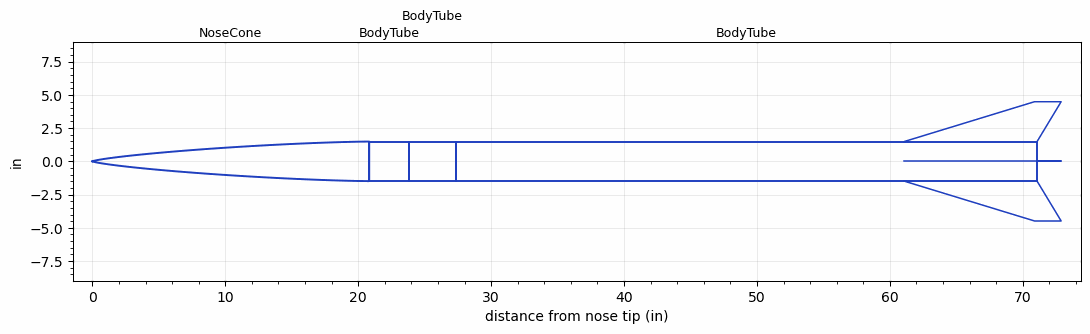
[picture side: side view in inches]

<RASAeroDocument>
 <FileVersion>2</FileVersion>
 <RocketDesign>
  <NoseCone>
   <Length>20.825</Length>
   <Diameter>2.975</Diameter>
   <Shape>Von Karman Ogive</Shape>
   <BluntRadius>0.025</BluntRadius>
   <Location>0</Location>
  </NoseCone>
  <BodyTube>
   <Length>3</Length>
   <Diameter>2.975</Diameter>
   <Location>20.825</Location>
  </BodyTube>
  <BodyTube>
   <Length>3.5</Length>
   <Diameter>2.975</Diameter>
   <Location>23.825</Location>
  </BodyTube>
  <BodyTube>
   <Length>43.748</Length>
   <Diameter>2.975</Diameter>
   <Location>27.325</Location>
   <Fin>
    <Count>4</Count>
    <Chord>10</Chord>
    <Span>3</Span>
    <SweepDistance>9.8125</SweepDistance>
    <TipChord>2</TipChord>
    <Thickness>0.24</Thickness>
    <LERadius>0.03</LERadius>
    <Location>10</Location>
    <AirfoilSection>Hexagonal</AirfoilSection>
    <FX1>0.9212</FX1>
    <FX3>0.9212</FX3>
   </Fin>
  </BodyTube>
  <Surface>Rough Camouflage Paint</Surface>
  <ModifiedBarrowman>True</ModifiedBarrowman>
  <Turbulence>True</Turbulence>
  <UseBooster1>False</UseBooster1>
  <UseBooster2>False</UseBooster2>
 </RocketDesign>
 <LaunchSite>
  <Altitude>3900</Altitude>
  <Pressure>0</Pressure>
  <RodAngle>0</RodAngle>
  <RodLength>10</RodLength>
  <Temperature>70</Temperature>
  <WindSpeed>5</WindSpeed>
 </LaunchSite>
 <Recovery>
  <Altitude1>3000</Altitude1>
  <Altitude2>2000</Altitude2>
  <DeviceType1>Parachute</DeviceType1>
  <DeviceType2>Parachute</DeviceType2>
  <Event1>False</Event1>
  <Event2>False</Event2>
  <Size1>24</Size1>
  <Size2>9</Size2>
  <EventType1>Altitude</EventType1>
  <EventType2>Apogee</EventType2>
  <CD1>2.1</CD1>
  <CD2>0.8</CD2>
 </Recovery>
 <MachAlt>
  <Item>0, 5000</Item>
  <Item>4.5, 60000</Item>
 </MachAlt>
 <SimulationList>
  <Simulation>
   <SustainerEngine>N3570CE  (Chase)</SustainerEngine>
   <SustainerLaunchWt>24.5</SustainerLaunchWt>
   <SustainerNozzleDiameter>2.5</SustainerNozzleDiameter>
   <SustainerCG>43</SustainerCG>
   <SustainerIgnitionDelay>0</SustainerIgnitionDelay>
   <Booster1SeparationDelay>0</Booster1SeparationDelay>
   <Booster1IgnitionDelay>0</Booster1IgnitionDelay>
   <IncludeBooster1>False</IncludeBooster1>
   <Booster2Delay>0</Booster2Delay>
   <IncludeBooster2>False</IncludeBooster2>
   <TimetoApogee>54.63684</TimetoApogee>
   <MaxAltitude>63061.08</MaxAltitude>
   <MaxVelocity>3898.808</MaxVelocity>
   <OptimumWt>20.825</OptimumWt>
   <OptimumMaxAlt>20.825</OptimumMaxAlt>
  </Simulation>
  <Simulation>
   <SustainerEngine>N2500CP  (Chase)</SustainerEngine>
   <SustainerLaunchWt>22</SustainerLaunchWt>
   <SustainerNozzleDiameter>2.5</SustainerNozzleDiameter>
   <SustainerCG>42.6</SustainerCG>
   <SustainerIgnitionDelay>0</SustainerIgnitionDelay>
   <Booster1SeparationDelay>0</Booster1SeparationDelay>
   <Booster1IgnitionDelay>0</Booster1IgnitionDelay>
   <IncludeBooster1>False</IncludeBooster1>
   <Booster2Delay>0</Booster2Delay>
   <IncludeBooster2>False</IncludeBooster2>
   <TimetoApogee>66.01569</TimetoApogee>
   <MaxAltitude>84387.34</MaxAltitude>
   <MaxVelocity>4372.384</MaxVelocity>
  </Simulation>
  <Simulation>
   <SustainerEngine>N2900CB  (Chase)</SustainerEngine>
   <SustainerLaunchWt>24.2</SustainerLaunchWt>
   <SustainerNozzleDiameter>2.5</SustainerNozzleDiameter>
   <SustainerCG>43.1</SustainerCG>
   <SustainerIgnitionDelay>0</SustainerIgnitionDelay>
   <Booster1SeparationDelay>0</Booster1SeparationDelay>
   <Booster1IgnitionDelay>0</Booster1IgnitionDelay>
   <IncludeBooster1>False</IncludeBooster1>
   <Booster2Delay>0</Booster2Delay>
   <IncludeBooster2>False</IncludeBooster2>
   <TimetoApogee>59.35604</TimetoApogee>
   <MaxAltitude>71313.13</MaxAltitude>
   <MaxVelocity>4221.602</MaxVelocity>
   <OptimumWt>20.99331</OptimumWt>
   <OptimumMaxAlt>20.99331</OptimumMaxAlt>
  </Simulation>
  <Simulation>
   <SustainerEngine>N2600CE  (Chase)</SustainerEngine>
   <SustainerLaunchWt>22</SustainerLaunchWt>
   <SustainerNozzleDiameter>2.5</SustainerNozzleDiameter>
   <SustainerCG>43.23</SustainerCG>
   <SustainerIgnitionDelay>0</SustainerIgnitionDelay>
   <Booster1SeparationDelay>0</Booster1SeparationDelay>
   <Booster1IgnitionDelay>0</Booster1IgnitionDelay>
   <IncludeBooster1>False</IncludeBooster1>
   <Booster2Delay>0</Booster2Delay>
   <IncludeBooster2>False</IncludeBooster2>
   <TimetoApogee>56.73648</TimetoApogee>
   <MaxAltitude>70116.66</MaxAltitude>
   <MaxVelocity>4839.931</MaxVelocity>
   <OptimumWt>18.615</OptimumWt>
   <OptimumMaxAlt>18.615</OptimumMaxAlt>
  </Simulation>
  <Simulation>
   <SustainerEngine>N3570CE  (Chase)</SustainerEngine>
   <SustainerLaunchWt>20.4</SustainerLaunchWt>
   <SustainerNozzleDiameter>2.5</SustainerNozzleDiameter>
   <SustainerCG>43.48</SustainerCG>
   <SustainerIgnitionDelay>0</SustainerIgnitionDelay>
   <Booster1SeparationDelay>0</Booster1SeparationDelay>
   <Booster1IgnitionDelay>0</Booster1IgnitionDelay>
   <IncludeBooster1>False</IncludeBooster1>
   <Booster2Delay>0</Booster2Delay>
   <IncludeBooster2>False</IncludeBooster2>
   <TimetoApogee>53.32706</TimetoApogee>
   <MaxAltitude>65878.36</MaxAltitude>
   <MaxVelocity>4827.908</MaxVelocity>
   <OptimumWt>21.93</OptimumWt>
   <OptimumMaxAlt>21.93</OptimumMaxAlt>
  </Simulation>
 </SimulationList>
</RASAeroDocument>
